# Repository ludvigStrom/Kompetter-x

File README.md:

# Kompetter-x
Stm32 based HID macro 4x4 keypad with magnetic encoder. 

**Roadmap:
* Define the Menu Structure: Start by defining the structure of your menu. This could be a simple list of options, or a more complex tree-like structure with submenus. Each menu item should have a name and a function that gets called when the item is selected.

* USB Encapsulation: Create a module that handles all the USB communication. This module should provide functions for sending different types of commands (e.g., volume up/down, key press, etc.). These functions will be called by the menu system when a certain option is selected.

* Display Encapsulation: Similarly, create a module for handling the display. This module should provide functions for displaying the current menu, highlighting the selected option, etc.

* Input Handling: You'll need a way to navigate through the menu and select options. This could be done using the keyboard and the encoder. For example, the encoder could be used to scroll through the options, and a certain key could be used to select an option. Reads the input devices and updates the menu system accordingly.

* State Machine: Implement a state machine that keeps track of the current state of the system (e.g., which menu is currently being displayed, which option is selected, etc.). The state machine should update the state based on the input from the user and call the appropriate functions from the USB and display modules.

* Menu Functionality: Implement the functionality for each menu option. This could involve sending a certain USB command, entering a submenu, etc.

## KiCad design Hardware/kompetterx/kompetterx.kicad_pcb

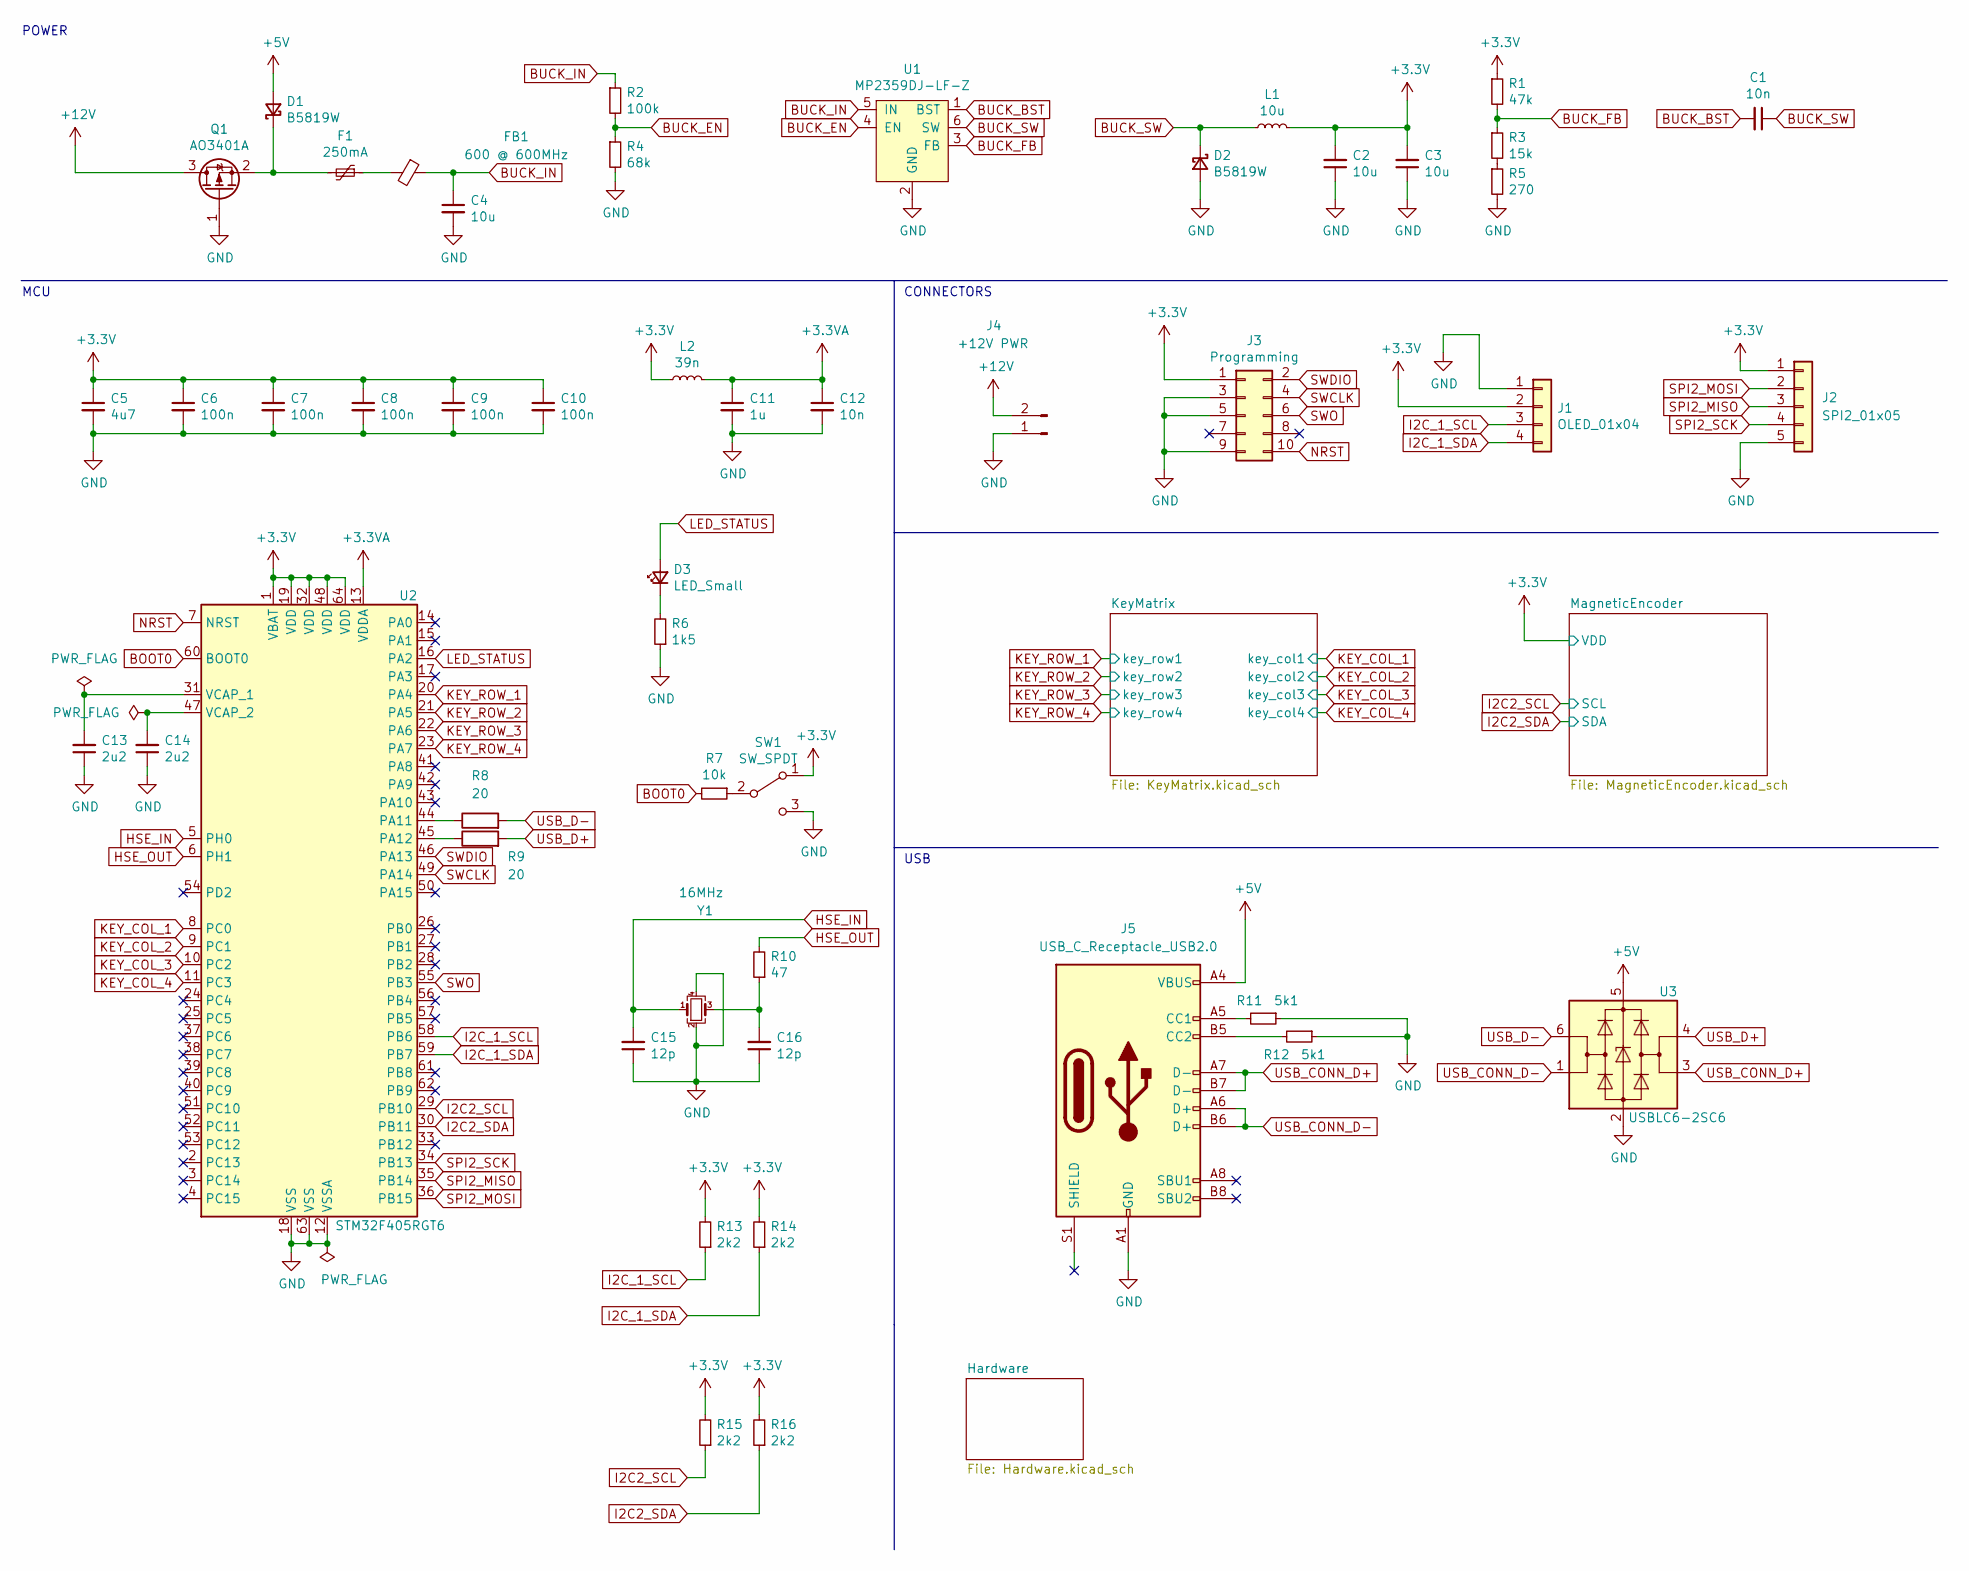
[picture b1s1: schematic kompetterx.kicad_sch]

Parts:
C1, C12: 10n; C_0603_1608Metric; LCSC C57112
C2, C3, C4: 10u; C_0805_2012Metric; LCSC C15850
C5: 4u7; C_0402_1005Metric; LCSC C23733
C6, C7, C8, C9, C10: 100n; C_0402_1005Metric; LCSC C1523
C11: 1u; C_0402_1005Metric; LCSC C52923
C13, C14: 2u2; C_0402_1005Metric; LCSC C12530
C15, C16: 12p; C_0402_1005Metric; LCSC C1547
D1, D2: B5819W; D_SOD-123; LCSC C8598
D3: LED_Small; LED_0805_2012Metric; LCSC C2297
F1: 250mA; Fuse_2920_7451Metric; LCSC C192524
FB1: 600 @ 600MHz; D_0805_2012Metric; LCSC C1017
J1: OLED_01x04; GM009606v42
J2: SPI2_01x05; PinHeader_1x05_P2.54mm_Vertical
J3: Programming; PinSocket_2x05_P1.27mm_Vertical
J4: +12V PWR; PinHeader_1x02_P2.54mm_Vertical
J5: USB_C_Receptacle_USB2.0; USB_C_Receptacle_HRO_TYPE-C-31-M-12; LCSC C165948
L1: 10u; L_Sunlord_SWPA252010S; LCSC C96806
L2: 39n; L_0402_1005Metric; LCSC C913698
Q1: AO3401A; SOT-23; LCSC C15127
R1: 47k; R_0805_2012Metric; LCSC C17713
R2: 100k; R_1206_3216Metric; LCSC C17900
R3: 15k; R_0402_1005Metric; LCSC C25756
R4: 68k; R_0402_1005Metric; LCSC C36871
R5: 270; R_0603_1608Metric; LCSC C22966
R6: 1k5; R_0402_1005Metric; LCSC C25867
R7: 10k; R_0402_1005Metric; LCSC C25744
R8, R9: 20; R_0603_1608Metric; LCSC C22950
R10: 47; R_0402_1005Metric; LCSC C25118
R11, R12: 5k1; R_0805_2012Metric; LCSC C27834
R13, R14, R15, R16: 2k2; R_0402_1005Metric; LCSC C25879
SW1: SW_SPDT; PinHeader_1x03_P2.54mm_Vertical
U1: MP2359DJ-LF-Z; SOT-23-6; LCSC C2959845
U2: STM32F405RGT6; LQFP-64_10x10mm_P0.5mm; LCSC C15742
U3: USBLC6-2SC6; SOT-23-6; LCSC C2687116
Y1: 16MHz; Oscillator_SMD_EuroQuartz_XO32-4Pin_3.2x2.5mm; LCSC C13738

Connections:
+3.3VA: C11.1, C12.1, L2.2, U2.13 (VDDA)
+3V3: C2.2, C3.2, C5.1, C6.1, C7.1, C8.1, C9.1, C10.1, J1.2, J2.1, J3.1, L1.2, L2.1, R1.1, R13.2, R14.2, R15.2, R16.2, SW1.1 (A), U2.1 (VBAT), U2.19 (VDD), U2.32 (VDD), U2.48 (VDD), U2.64 (VDD); also elsewhere on the board
+5V: D1.2 (A), J5.A4 (VBUS), J5.A9 (VBUS), J5.B4 (VBUS), J5.B9 (VBUS), U3.5 (VBUS); also elsewhere on the board
BOOT0: R7.2, U2.60 (BOOT0)
BUCK_BST: C1.2, U1.1 (BST)
BUCK_EN: R2.2, R4.1, U1.4 (EN)
BUCK_FB: R1.2, R3.1, U1.3 (FB)
BUCK_IN: C4.1, FB1.1, R2.1, U1.5 (IN)
BUCK_SW: C1.1, D2.1 (K), L1.1, U1.6 (SW)
GND: C2.1, C3.1, C4.2, C5.2, C6.2, C7.2, C8.2, C9.2, C10.2, C11.2, C12.2, C13.1, C14.1, C15.1, C16.1, D2.2 (A), J1.1, J2.5, J3.3, J3.5, J3.9, J4.1, J5.A1 (GND), J5.A12 (GND), J5.B1 (GND), J5.B12 (GND), Q1.1 (G), R4.2, R5.2, R6.1, R11.1, R12.1, SW1.3 (C), U1.2 (GND), U2.12 (VSSA), U2.18 (VSS), U2.63 (VSS), U3.2 (GND), Y1.2, Y1.4; also elsewhere on the board
HSE_IN: C15.2, U2.5 (PH0), Y1.1
HSE_OUT: R10.2, U2.6 (PH1)
I2C2_SCL: R15.1, U2.29 (PB10); also elsewhere on the board
I2C2_SDA: R16.1, U2.30 (PB11); also elsewhere on the board
I2C_1_SCL: J1.3, R13.1, U2.58 (PB6)
I2C_1_SDA: J1.4, R14.1, U2.59 (PB7)
KEY_COL_1: U2.8 (PC0); also elsewhere on the board
KEY_COL_2: U2.9 (PC1); also elsewhere on the board
KEY_COL_3: U2.10 (PC2); also elsewhere on the board
KEY_COL_4: U2.11 (PC3); also elsewhere on the board
KEY_ROW_1: U2.20 (PA4); also elsewhere on the board
KEY_ROW_2: U2.21 (PA5); also elsewhere on the board
KEY_ROW_3: U2.22 (PA6); also elsewhere on the board
KEY_ROW_4: U2.23 (PA7); also elsewhere on the board
LED_STATUS: D3.2 (A), U2.16 (PA2)
NRST: J3.10, U2.7 (NRST)
unnamed: C16.2, R10.1, Y1.3
unnamed: D1.1 (K), F1.2, Q1.2 (S)
unnamed: D3.1 (K), R6.2
unnamed: F1.1, FB1.2
unnamed: J4.2, Q1.3 (D)
unnamed: J5.A5 (CC1), R11.2
unnamed: J5.B5 (CC2), R12.2
unnamed: R3.2, R5.1
unnamed: R7.1, SW1.2 (B)
unnamed: R8.1, U2.44 (PA11)
unnamed: R9.1, U2.45 (PA12)
unnamed: C13.2, U2.31 (VCAP_1)
unnamed: C14.2, U2.47 (VCAP_2)
SPI2_MISO: J2.3, U2.35 (PB14)
SPI2_MOSI: J2.2, U2.36 (PB15)
SPI2_SCK: J2.4, U2.34 (PB13)
SWCLK: J3.4, U2.49 (PA14)
SWDIO: J3.2, U2.46 (PA13)
SWO: J3.6, U2.55 (PB3)
USB_D+: R9.2, U3.4 (I/O2)
USB_D-: R8.2, U3.6 (I/O1)

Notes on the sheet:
USB
POWER
CONNECTORS
MCU

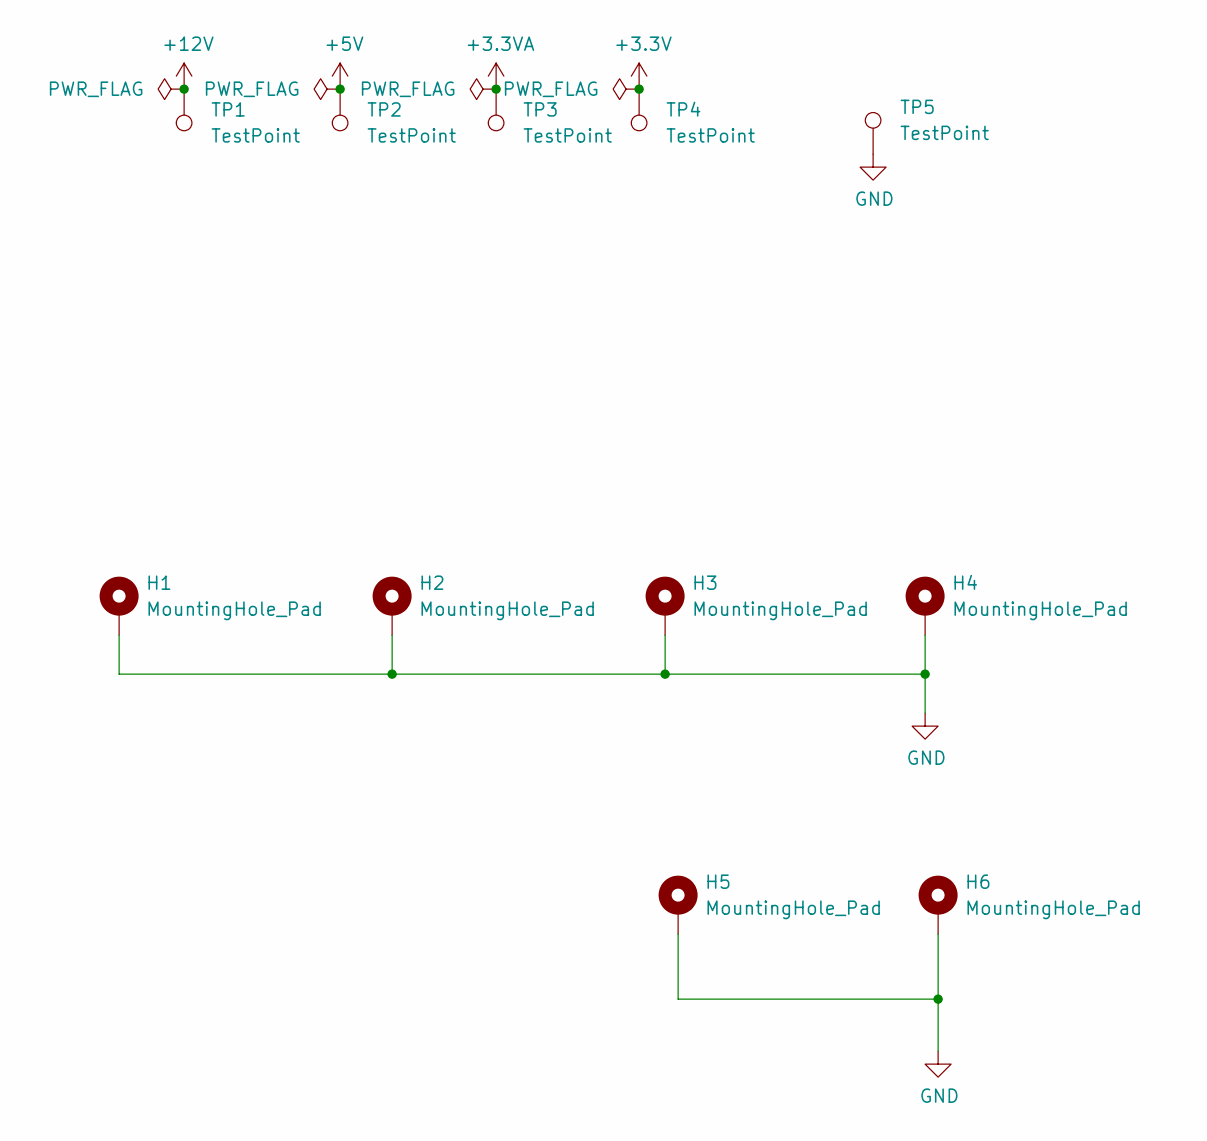
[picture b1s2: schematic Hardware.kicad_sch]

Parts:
H1, H2, H3, H4, H5, H6: MountingHole_Pad; MountingHole_3.2mm_M3_DIN965_Pad
TP1, TP2, TP3, TP4, TP5: TestPoint; TestPoint_Plated_Hole_D2.0mm

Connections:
+5V: TP2.1; also elsewhere on the board
GND: H1.1, H2.1, H3.1, H4.1, H5.1, H6.1, TP5.1; also elsewhere on the board

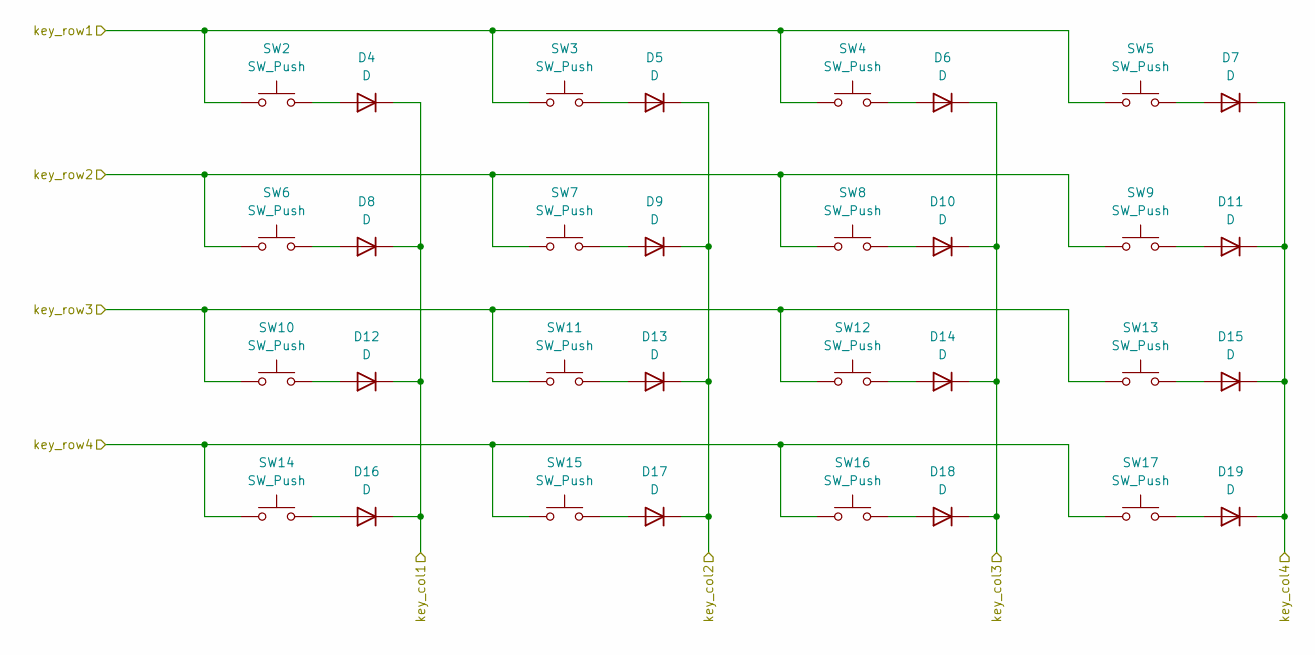
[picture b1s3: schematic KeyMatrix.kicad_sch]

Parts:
D4, D5, D6, D7, D8, D9, D10, D11, D12, D13, D14, D15, D16, D17, D18, D19: D; D_SOD-123; LCSC C81598
SW2, SW3, SW4, SW5, SW6, SW7, SW8, SW9, SW10, SW11, SW12, SW13, SW14, SW15, SW16, SW17: SW_Push; SW_Cherry_MX_1.00u_PCB

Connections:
KEY_COL_1: D4.1 (K), D8.1 (K), D12.1 (K), D16.1 (K); also elsewhere on the board
KEY_COL_2: D5.1 (K), D9.1 (K), D13.1 (K), D17.1 (K); also elsewhere on the board
KEY_COL_3: D6.1 (K), D10.1 (K), D14.1 (K), D18.1 (K); also elsewhere on the board
KEY_COL_4: D7.1 (K), D11.1 (K), D15.1 (K), D19.1 (K); also elsewhere on the board
KEY_ROW_1: SW2.1, SW3.1, SW4.1, SW5.1; also elsewhere on the board
KEY_ROW_2: SW6.1, SW7.1, SW8.1, SW9.1; also elsewhere on the board
KEY_ROW_3: SW10.1, SW11.1, SW12.1, SW13.1; also elsewhere on the board
KEY_ROW_4: SW14.1, SW15.1, SW16.1, SW17.1; also elsewhere on the board
unnamed: D4.2 (A), SW2.2
unnamed: D5.2 (A), SW3.2
unnamed: D6.2 (A), SW4.2
unnamed: D7.2 (A), SW5.2
unnamed: D8.2 (A), SW6.2
unnamed: D9.2 (A), SW7.2
unnamed: D10.2 (A), SW8.2
unnamed: D11.2 (A), SW9.2
unnamed: D12.2 (A), SW10.2
unnamed: D13.2 (A), SW11.2
unnamed: D14.2 (A), SW12.2
unnamed: D15.2 (A), SW13.2
unnamed: D16.2 (A), SW14.2
unnamed: D17.2 (A), SW15.2
unnamed: D18.2 (A), SW16.2
unnamed: D19.2 (A), SW17.2

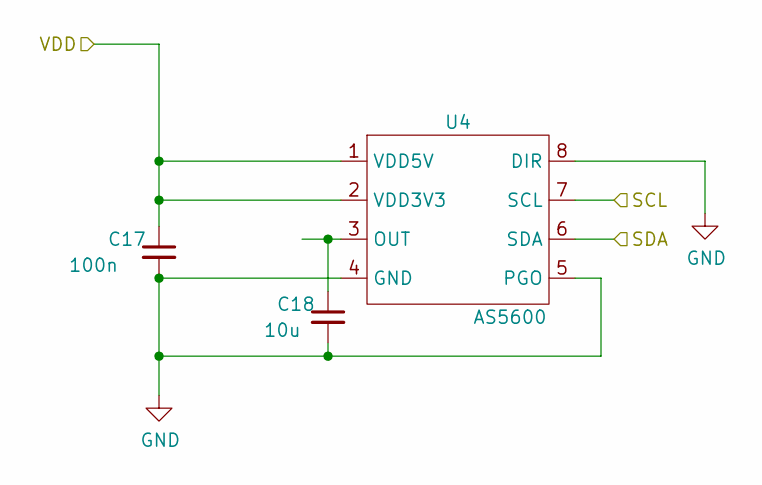
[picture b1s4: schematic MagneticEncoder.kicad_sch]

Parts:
C17: 100n; C_0402_1005Metric; LCSC C1523
C18: 10u; C_0805_2012Metric; LCSC C15850
U4: AS5600; SOIC-8_3.9x4.9mm_P1.27mm; LCSC C499458

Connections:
+3V3: C17.1, U4.1 (VDD5V), U4.2 (VDD3V3); also elsewhere on the board
GND: C17.2, C18.2, U4.4 (GND), U4.5 (PGO), U4.8 (DIR); also elsewhere on the board
I2C2_SCL: U4.7 (SCL); also elsewhere on the board
I2C2_SDA: U4.6 (SDA); also elsewhere on the board
unnamed: C18.1, U4.3 (OUT)

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
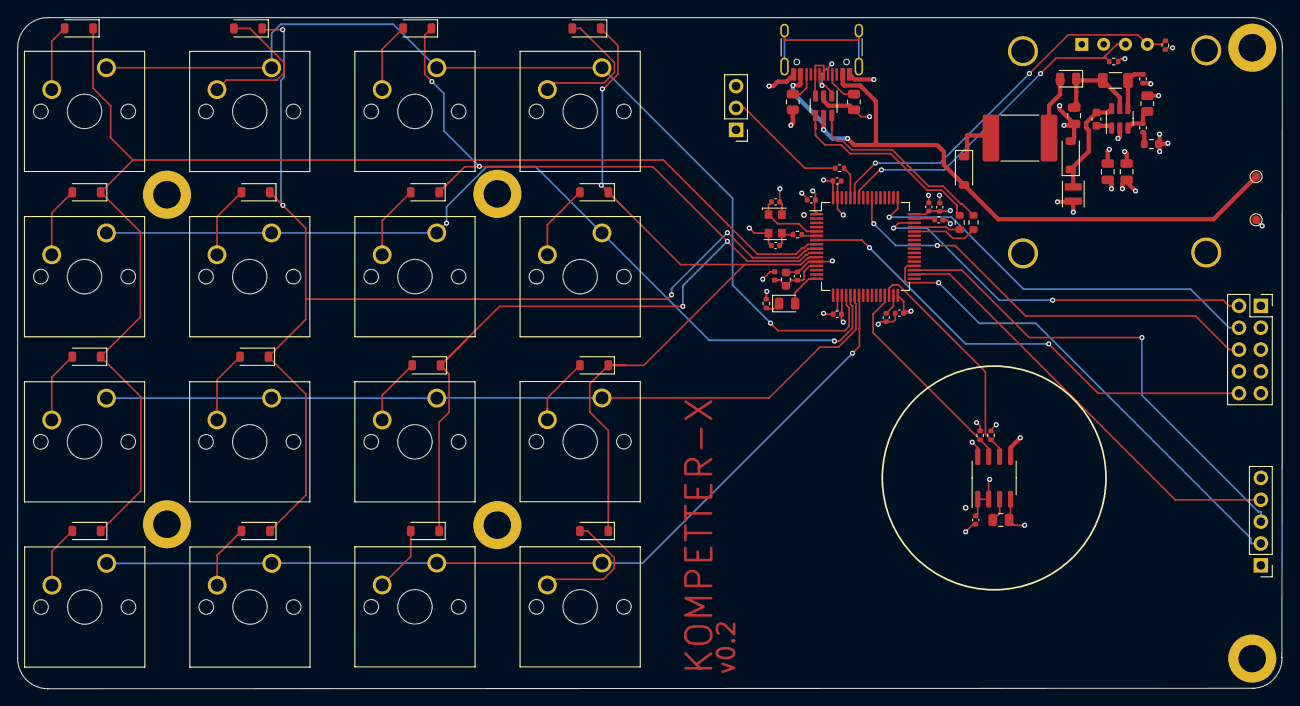
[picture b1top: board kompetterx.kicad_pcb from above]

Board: 4 copper layers, 147.0 x 78.0 mm, 91 parts (0 on the bottom side), 65 nets.

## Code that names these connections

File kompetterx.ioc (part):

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Mcu.Name=STM32F405RGTx
Mcu.Package=LQFP64
Mcu.UserName=STM32F405RGTx
PA11.Mode=Device_Only
PA11.Signal=USB_OTG_FS_DM
PA12.Mode=Device_Only
PA12.Signal=USB_OTG_FS_DP
PA13.Mode=Trace_Asynchronous_SW
PA13.Signal=SYS_JTMS-SWDIO
PA14.Mode=Trace_Asynchronous_SW
PA14.Signal=SYS_JTCK-SWCLK
PA2.GPIOParameters=PinState,GPIO_Label
PA2.GPIO_Label=LED_STATUS
PA2.PinState=GPIO_PIN_RESET
PA2.Signal=GPIO_Output
PA4.GPIOParameters=GPIO_Label
PA4.GPIO_Label=KEY_ROW_1
PA4.Signal=GPIO_Output
PA5.GPIOParameters=GPIO_Label
PA5.GPIO_Label=KEY_ROW_2
PA5.Signal=GPIO_Output
PA6.GPIOParameters=GPIO_Label
PA6.GPIO_Label=KEY_ROW_3
PA6.Signal=GPIO_Output
PA7.GPIOParameters=GPIO_Label
PA7.GPIO_Label=KEY_ROW_4
PA7.Signal=GPIO_Output
PB10.GPIOParameters=GPIO_PuPdOD
PB10.GPIO_PuPdOD=GPIO_NOPULL
PB10.Mode=I2C
PB10.Signal=I2C2_SCL
PB11.GPIOParameters=GPIO_PuPdOD
PB11.GPIO_PuPdOD=GPIO_NOPULL
PB11.Mode=I2C
PB11.Signal=I2C2_SDA
PB13.Mode=Full_Duplex_Master
PB13.Signal=SPI2_SCK
PB14.Mode=Full_Duplex_Master
PB14.Signal=SPI2_MISO
PB15.Mode=Full_Duplex_Master
PB15.Signal=SPI2_MOSI
PB3.Mode=Trace_Asynchronous_SW
PB3.Signal=SYS_JTDO-SWO
PB6.GPIOParameters=GPIO_Speed,GPIO_PuPdOD,GPIO_Mode
PB6.GPIO_Mode=GPIO_MODE_AF_OD
PB6.GPIO_PuPdOD=GPIO_NOPULL
PB6.GPIO_Speed=GPIO_SPEED_FREQ_VERY_HIGH
PB6.Mode=I2C
PB6.Signal=I2C1_SCL
PB7.GPIOParameters=GPIO_Speed,GPIO_PuPdOD,GPIO_Mode
PB7.GPIO_Mode=GPIO_MODE_AF_OD
PB7.GPIO_PuPdOD=GPIO_NOPULL
PB7.GPIO_Speed=GPIO_SPEED_FREQ_VERY_HIGH
PB7.Mode=I2C
PB7.Signal=I2C1_SDA
PC0.GPIOParameters=GPIO_Label
PC0.GPIO_Label=KEY_COL_1
PC0.Signal=GPXTI0
PC1.GPIOParameters=GPIO_Label
PC1.GPIO_Label=KEY_COL_2
PC1.Signal=GPXTI1
PC2.GPIOParameters=GPIO_Label
PC2.GPIO_Label=KEY_COL_3
PC2.Signal=GPXTI2
PC3.GPIOParameters=GPIO_Label
PC3.GPIO_Label=KEY_COL_4
PC3.Signal=GPXTI3
PH0-OSC_IN.Mode=HSE-External-Oscillator
PH0-OSC_IN.Signal=RCC_OSC_IN
PH1-OSC_OUT.Mode=HSE-External-Oscillator
PH1-OSC_OUT.Signal=RCC_OSC_OUT
RCC.HSE_VALUE=16000000
RCC.SYSCLKFreq_VALUE=168000000
RCC.SYSCLKSource=RCC_SYSCLKSOURCE_PLLCLK
board=custom

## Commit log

2023-06-25 Update USB-bug hardware + software
2023-06-28 Send off v0.2 to JLCPB
2023-07-11 Update to magnet status
2023-07-12 New USB HID handling
2023-07-13 Interrupts
2023-07-13 Current state
2023-07-13 HID debounce update
2023-07-13 update to HEX Hid codes
2023-07-13 bug fix
2023-07-13 working debounce matrix scan
2023-07-13 code cleanup
2023-07-14 LED flashing when sending report
2023-07-14 encoder smoothing and limiting
2023-07-14 Keyboard working but not mouse
2023-07-14 update to mouse
2023-07-19 added utils file separation
2023-07-20 Fixing scroll
2023-07-20 Keymaps
2023-07-20 alpha smoothing
2023-07-21 added keyboardscanner files
2023-07-21 Refactor of keyboard scanning
2023-07-21 angle sensor refactor
2023-07-21 Fixed warnings
2023-07-27 USB Hid report encapsulation
2023-07-27 Deleted Boilerplate comments from cubeMX
2023-07-28 dispaly
2023-07-28 Cleanup macros and modkeys
2023-07-29 HID descriptor and broken out event
